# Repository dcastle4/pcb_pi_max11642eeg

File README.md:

# Maxim MAX11642EEG ADC PCB for the Pi

This repo contains KiCad design files for an ADC board for the Raspberry Pi. The board uses a MAX11642EEG by Maxim which allows for 16 inputs, all of which are mapped to the first two screw terminals. The last screw terminal carries +5V and ground leads.

A picture of the PCB from Pcbnew's 3D viewer can be seen here:

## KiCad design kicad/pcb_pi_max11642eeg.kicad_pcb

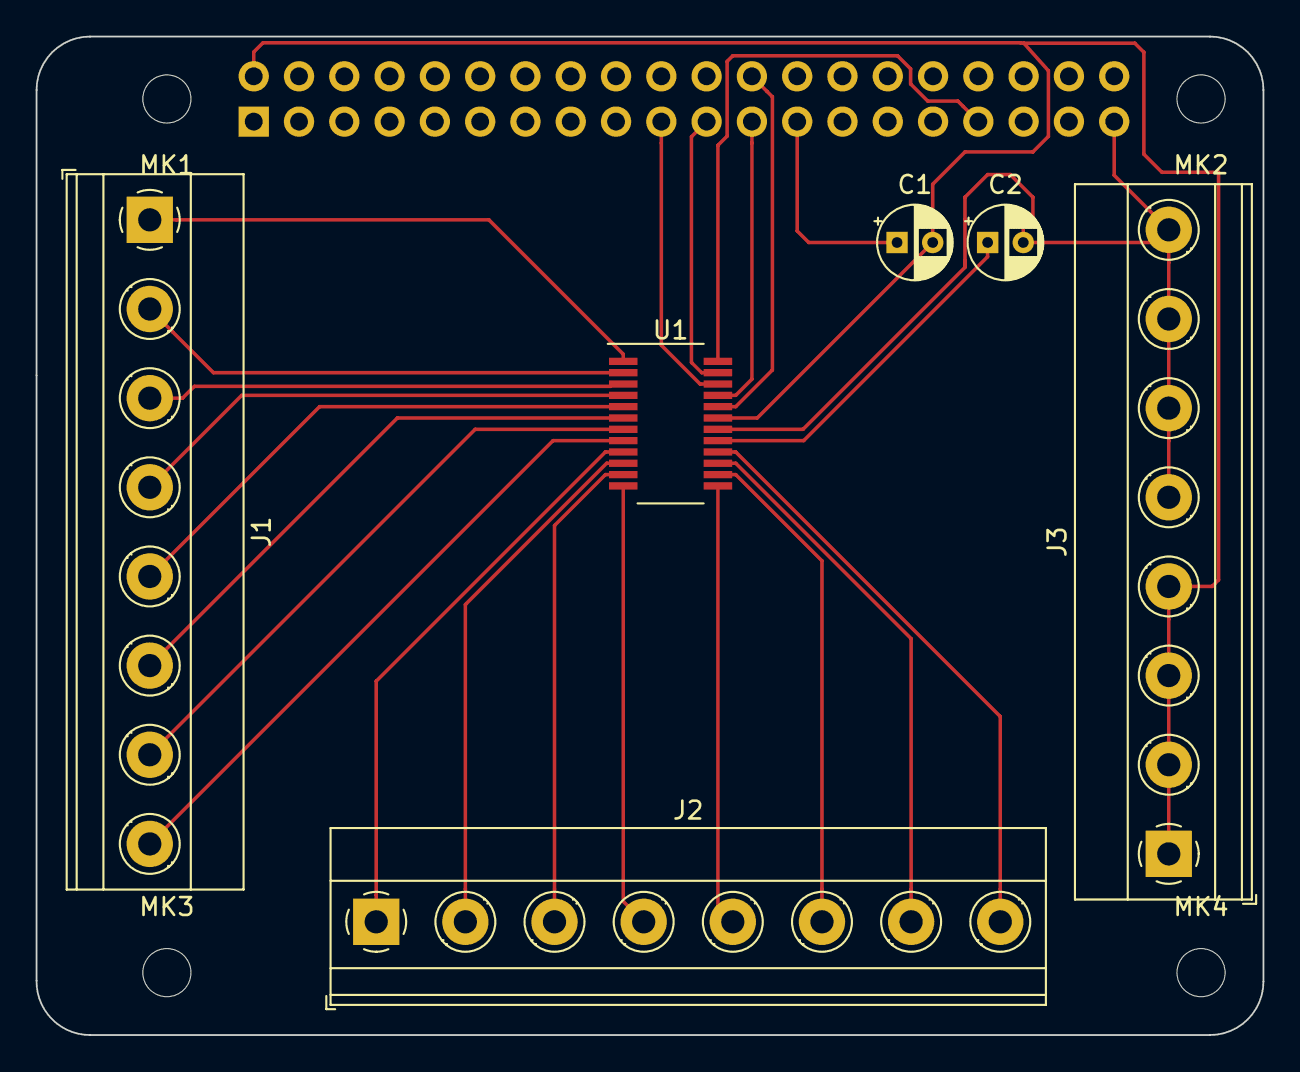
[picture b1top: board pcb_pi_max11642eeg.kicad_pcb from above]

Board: 2 copper layers, 68.8 x 56.0 mm, 11 parts (1 on the bottom side), 25 nets.

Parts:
C1, C2: 0.1uF; CP_Radial_D4.0mm_P2.00mm
J1, J2, J3: Screw_Terminal_01x08; TerminalBlock_Phoenix_MKDS-1,5-8_1x08_P5.00mm_Horizontal
MK1, MK2, MK3, MK4: M2.5; MountingHole_2.7mm_M2.5
P1: Conn_02x20_Odd_Even; PinSocket_2x20_P2.54mm_Vertical
U1: MAX11642EEG; QSOP-24_3.9x8.7mm_P0.635mm

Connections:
+3V3: P1.1, P1.17
+5V: C1.2, J3.1, J3.2, J3.3, J3.4, P1.2, P1.4, U1.19
/AIN0: J1.1, U1.1
/AIN1: J1.2, U1.2
/AIN2: J1.3, U1.3
/AIN3: J1.4, U1.4
/AIN4: J1.5, U1.5
/AIN5: J1.6, U1.6
/AIN6: J1.7, U1.7
/AIN7: J1.8, U1.8
/AIN8: J2.1, U1.9
/AIN9: J2.2, U1.10
/AIN10: J2.3, U1.11
/AIN11: J2.4, U1.12
/AIN12: J2.5, U1.13
/AIN13: J2.6, U1.14
/AIN14: J2.7, U1.15
/AIN15: J2.8, U1.16
/CS: P1.24, U1.20
/DIN: P1.19, U1.22
/DOUT: P1.21, U1.23
/EOC: P1.33, U1.24
/SCK: P1.23, U1.21
GND: C1.1, C2.2, J3.5, J3.6, J3.7, J3.8, P1.6, P1.9, P1.14, P1.20, P1.25, P1.30, P1.34, P1.39, U1.18
unnamed: C2.1, U1.17

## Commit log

2020-11-22 Initial commit to git
2020-11-26 Organized file hierarchy, added README with picture
2020-11-26 Removed files from root directory
